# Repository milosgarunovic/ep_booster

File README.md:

# ep_booster

KiCad project for EP Booster

---

The idea with this project is to have it in one place, with some "standards" like to view everything
in KiCad and export for manufacturing.

As a bassist, I'm using EP Booster as always on pedal in vintage mode without a boost, and it gives
a nice warmth to my custom bass with jazz pickups, and better thump with my Squier VM Precision with
Wilde P-46 pickup.

What I want to do as a first version is to have the whole thing as a pedal, and then strip away the
parts that are for boost and just leave the vintage part in there so I can put it into my basses,
thus removing one pedal from signal chain.

---

Resources for the project:

- https://www.taydakits.com/instructions/ep-booster/pages/designators-and-components--20
- https://revolutiondeux.blogspot.com/2012/01/xotic-ep-booster.html
- http://toshi.life.coocan.jp/review/en_diy_booster_surface_mount.html
- https://www.amp-fx.de/ep-preamp-booster-en.htm (this one is interesting because it has more caps to change the
  characteristic of the vintage mode)
- https://guitar-electronics.eu/en_US/p/EP-BOOSTER-kit-ULTRA/408

---

From the first source, here's the BOM

## Capacitors (POLYESTER FILM BOX TYPE CAPACITOR)

- C1 47NF 100V 5% POLYESTER FILM BOX TYPE CAPACITOR
- C5 3.3NF 100V 5% POLYESTER FILM BOX TYPE CAPACITOR

## Capacitors (ELECTROLYTIC CAPACITOR 5X11MM)

- C2 10UF 50V ELECTROLYTIC CAPACITOR 5X11MM
- C3 10UF 50V ELECTROLYTIC CAPACITOR 5X11MM (Original)
- C3 0.1UF 50V ELECTROLYTIC CAPACITOR 5X11MM  (Remove more bass)
- C6 10UF 50V ELECTROLYTIC CAPACITOR 5X11MM
- C7 10UF 50V ELECTROLYTIC CAPACITOR 5X11MM
- C8 47UF 25V ELECTROLYTIC CAPACITOR 5X11MM

## Capacitors (ELECTROLYTIC CAPACITOR 6X11MM)

- C4 100UF 35V ELECTROLYTIC CAPACITOR 6X11MM

## Diode

- D1 1N4148 1N4148 SWITCHING SIGNAL DIODE

## Transistors

- Q1 J201 SMD SOT-23 J201 JFET N-CHANNEL TRANSISTOR
- Q2 2N5088 2N5088 GERENAL PURPOSE TRANSISTOR

## Resistors

- R1 1M OHM 1/4W 1% METAL FILM RESISTOR
- R2 33K OHM 1/4W 1% METAL FILM RESISTOR
- R3 1M OHM 1/4W 1% METAL FILM RESISTOR
- R4 50k Trimmer 50K TRIMMER POTENTIOMETER
- R5 4.7K OHM 1/4W 1% METAL FILM RESISTOR
- R6 1K OHM 1/4W 1% METAL FILM RESISTOR
- R7 15K OHM 1/4W 1% METAL FILM RESISTOR  (Original)
- R7 33K OHM 1/4W 1% METAL FILM RESISTOR  (Remove more treble)
- R8 10K OHM 1/4W 1% METAL FILM RESISTOR
- R9 1M OHM 1/4W 1% METAL FILM RESISTOR
- R10 10K OHM 1/4W 1% METAL FILM RESISTOR
- R11 10K OHM 1/4W 1% METAL FILM RESISTOR
- R12 47K OHM 1/4W 1% METAL FILM RESISTOR
- R13 100 OHM 1/4W 1% METAL FILM RESISTOR

## Potentiometer

- GAIN 10k-C 10K OHM ANTI-LOG POTENTIOMETER

## Switches

- S1 (Bass) - MINI SLIDE SWITCH SPDT ON-ON (Vintage?)
- S2 (Treble) - MINI SLIDE SWITCH SPDT ON-ON (Bright?)

BIAS

Adjust R4 for biasing. The original value of R4 is 8.2k Ohm.

MODIFICATIONS

The original bass and treble switches do not have noticeable effect. To remove more bass, reduce C3 capacitance (e.g.
0.1 uF). To remove more treble, increase R7 resistance (e.g. 33k).

SWITCHES

The PCB allows to mount 4.7mm pitch switches inside the enclosure.

S1 (Bass)       MINI SLIDE SWITCH SPDT
S2 (Treble)     MINI SLIDE SWITCH SPDT

If no switches are required, no need to mount C4 and R7.

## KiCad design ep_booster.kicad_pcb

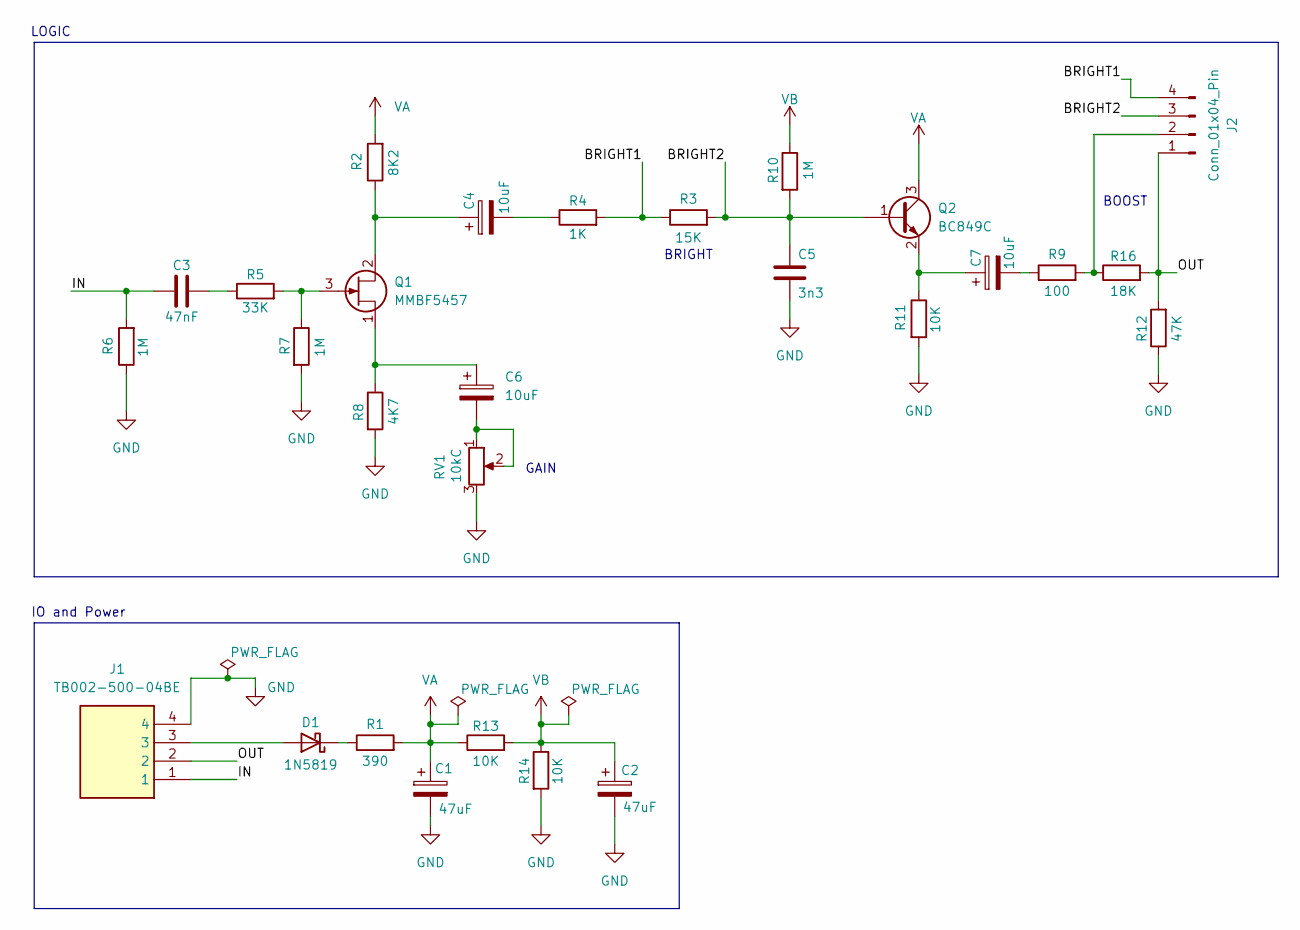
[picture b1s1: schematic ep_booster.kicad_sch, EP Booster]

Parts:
C1, C2: 47uF; CP_Radial_D6.3mm_P2.50mm
C3: 47nF; C_Rect_L7.2mm_W2.5mm_P5.00mm_FKS2_FKP2_MKS2_MKP2
C4, C6, C7: 10uF; CP_Radial_D5.0mm_P2.50mm
C5: 3n3; C_Rect_L7.2mm_W3.0mm_P5.00mm_FKS2_FKP2_MKS2_MKP2
D1: 1N5819; D_DO-41_SOD81_P7.62mm_Horizontal
J1: TB002-500-04BE; TB00250004BE; Mouser Part Number 490-TB002-500-04BE
J2: Conn_01x04_Pin; PinHeader_1x04_P2.54mm_Vertical
Q1: MMBF5457; SOT-23
Q2: BC849C; SOT-23
R1: 390; R_1206_3216Metric_Pad1.30x1.75mm_HandSolder
R2: 8K2; R_1206_3216Metric_Pad1.30x1.75mm_HandSolder
R3: 15K; R_1206_3216Metric_Pad1.30x1.75mm_HandSolder
R4: 1K; R_1206_3216Metric_Pad1.30x1.75mm_HandSolder
R5: 33K; R_1206_3216Metric_Pad1.30x1.75mm_HandSolder
R6, R7, R10: 1M; R_1206_3216Metric_Pad1.30x1.75mm_HandSolder
R8: 4K7; R_1206_3216Metric_Pad1.30x1.75mm_HandSolder
R9: 100; R_1206_3216Metric_Pad1.30x1.75mm_HandSolder
R11, R13, R14: 10K; R_1206_3216Metric_Pad1.30x1.75mm_HandSolder
R12: 47K; R_1206_3216Metric_Pad1.30x1.75mm_HandSolder
R16: 18K; R_1206_3216Metric_Pad1.30x1.75mm_HandSolder
RV1: 10kC; 3362S1103LF

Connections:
/BRIGHT1: J2.4, R3.1, R4.2
/BRIGHT2: C5.1, J2.3, Q2.1 (B), R3.2, R10.2
/IN: C3.1, J1.1, R6.2
/OUT: J1.2, J2.1, R12.2, R16.2
GND: C1.2, C2.2, C5.2, J1.4, R6.1, R7.2, R8.2, R11.2, R12.1, R14.2, RV1.3
unnamed: C3.2, R5.1
unnamed: C4.2, R4.1
unnamed: C6.2, RV1.1, RV1.2
unnamed: C7.2, R9.1
unnamed: D1.2 (A), J1.3
unnamed: D1.1 (K), R1.1
unnamed: J2.2, R9.2, R16.1
unnamed: C4.1, Q1.2 (D), R2.1
unnamed: Q1.3 (G), R5.2, R7.1
unnamed: C6.1, Q1.1 (S), R8.1
unnamed: C7.1, Q2.2 (E), R11.1
VA: C1.1, Q2.3 (C), R1.2, R2.2, R13.1
VB: C2.1, R10.1, R13.2, R14.1

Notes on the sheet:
BOOST
BRIGHT
GAIN
IO and Power
LOGIC

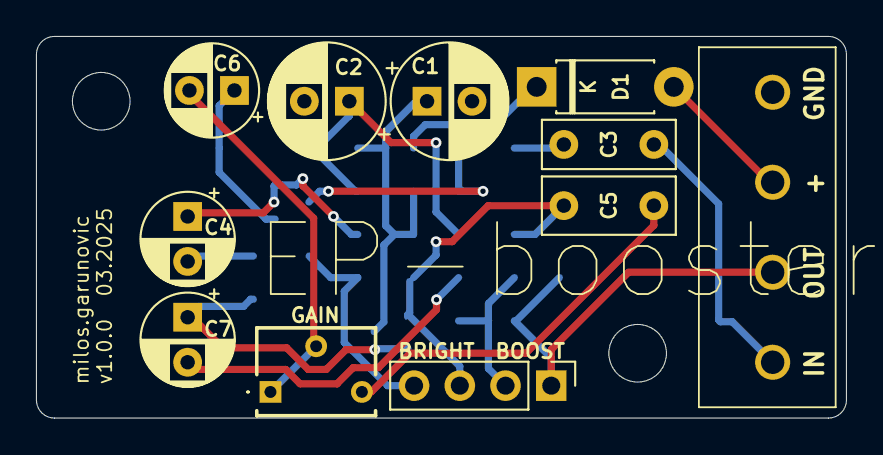
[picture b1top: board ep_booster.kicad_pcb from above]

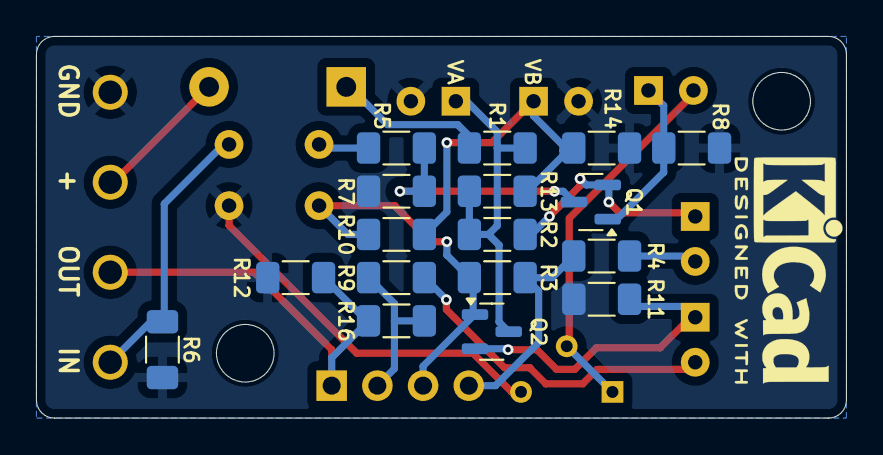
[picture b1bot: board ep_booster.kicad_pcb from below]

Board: 2 copper layers, 45.0 x 21.2 mm, 28 parts (17 on the bottom side), 18 nets.

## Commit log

2024-12-16 readme update
2024-12-16 updated readme and added initial kicad files
2024-12-16 schema added
2025-01-05 traced board from aionfx
2025-01-06 footprint association
2025-01-31 libs and pcb design update
2025-02-03 libs and pcb design update (2)
2025-02-03 docs update
2025-02-03 changed pot to bourns 3362S
2025-02-03 component placement update
2025-02-23 schematic design finished according to checklist
2025-02-23 added 9v battery outline on User.1 layer for reference
2025-02-23 refactored layout and added 2 mounting holes for M3 screws
2025-02-23 replaced two 1x02 pin headers with 1x04
2025-02-23 tracing and copper field (GND) added
2025-02-23 silkscreen f and b done
2025-02-23 silkscreen text and graphics + docs update
2025-02-23 added board dimensions on User.1 layer and 3D image to docs
2025-02-25 C5 updated footprint 2.5->3mm width
2025-02-27 increase track width to minimum 0.3mm, add VA and VB debug silkscreen
2025-02-27 B.Silkscreen thickened and aligned better
2025-02-27 increase track width to 0.4mm
2025-02-27 add F.Silkscreen for IO, update C ref des
2025-02-27 finalizing updates
2025-02-27 gerber export (kicad plugin)
2025-03-09 update checklist, add graphics, add date variable
2025-03-09 Revert "update checklist, add graphics, add date variable"
    This reverts commit 718c29c54fdfbd260644ec6b42491cfe9fa2302f.
